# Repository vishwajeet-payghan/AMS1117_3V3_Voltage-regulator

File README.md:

# AMS1117-3.3V Voltage Regulator PCB

A compact PCB designed using the **AMS1117-3.3V voltage regulator** to convert an input DC voltage into a stable, regulated **3.3V DC output**. The board supports an input voltage range of **4V to 12V DC** and includes input and output filter capacitors for improved voltage stability.

### Features

- **Voltage Regulator:** AMS1117-3.3V
- **Input Voltage:** 4V–12V DC
- **Output Voltage:** Fixed 3.3V DC
- **Input Capacitors:** 0.1µF and 10µF
- **Output Capacitors:** 0.1µF and 10µF
- **PCB Dimensions:** 13.04 mm × 31.95 mm
- **Input/Output:** 2-pin connectors for easy interfacing

### Applications

- Power supply for ESP32 and other microcontrollers
- Arduino and embedded electronics projects
- 3.3V sensors and peripheral modules
- Prototyping and electronics development

### Note

As the AMS1117-3.3V is a linear regulator, the voltage difference between input and output is dissipated as heat. Ensure adequate thermal management and do not exceed the regulator's current and thermal limits.

**Designed for compact, simple, and reliable 3.3V power regulation.**

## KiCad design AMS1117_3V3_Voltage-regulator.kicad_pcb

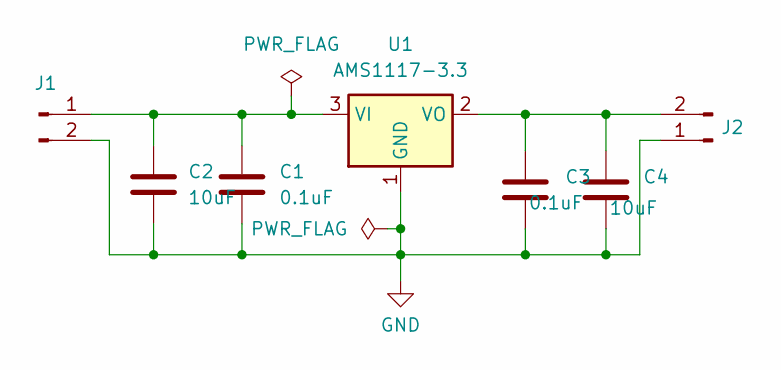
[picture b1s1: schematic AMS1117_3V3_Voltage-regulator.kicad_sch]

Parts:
C1, C3: 0.1uF; C_0603_1608Metric
C2, C4: 10uF; C_0603_1608Metric
J1, J2: Conn_01x02_Pin; PinHeader_1x02_P2.54mm_Vertical
U1: AMS1117-3.3; SOT-223-3_TabPin2

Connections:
GND: C1.2, C2.2, C3.2, C4.2, J1.2, J2.1, U1.1 (GND)
unnamed: C1.1, C2.1, J1.1, U1.3 (VI)
unnamed: C3.1, C4.1, J2.2, U1.2 (VO)

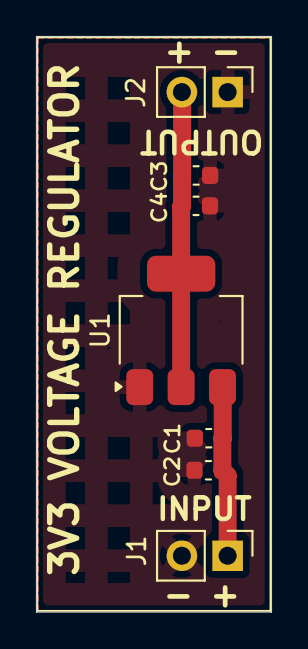
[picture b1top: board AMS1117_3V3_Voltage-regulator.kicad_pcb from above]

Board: 2 copper layers, 13.1 x 32.0 mm, 7 parts (0 on the bottom side), 3 nets.
